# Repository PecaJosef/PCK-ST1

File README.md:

# PCK-ST1
Star tracker with automatic polar alignment

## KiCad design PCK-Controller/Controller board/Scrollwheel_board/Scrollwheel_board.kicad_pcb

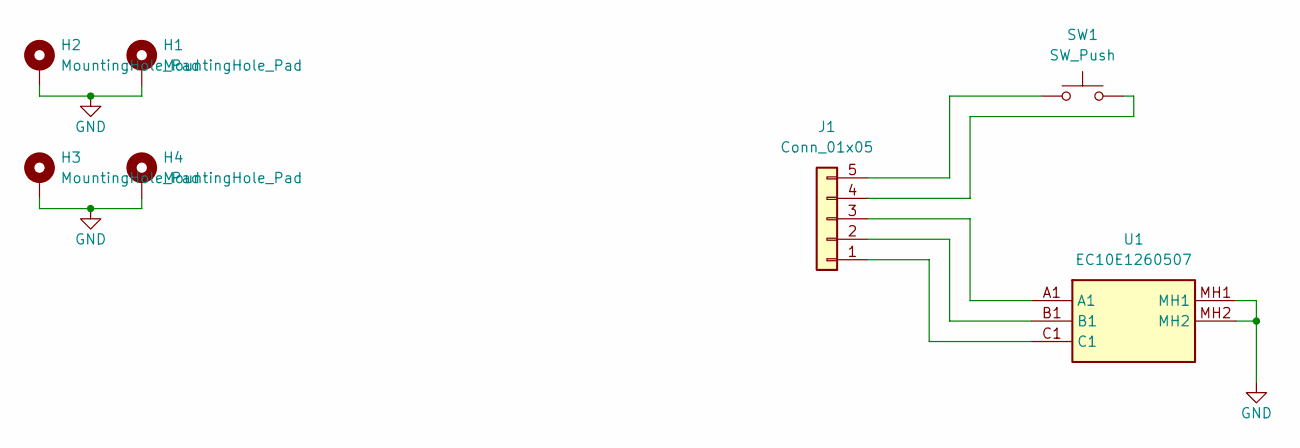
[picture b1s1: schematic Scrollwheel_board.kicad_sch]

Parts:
H1, H2, H3, H4: MountingHole_Pad; MountingHole_3.2mm_M3_DIN965_Pad
J1: Conn_01x05; JST_PH_B5B-PH-K_1x05_P2.00mm_Vertical
SW1: SW_Push; SW_SPST_PTS645Sx43SMTR92
U1: EC10E1260507; Mouser Part Number 688-EC10E1260507

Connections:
GND: H1.1, H2.1, H3.1, H4.1, U1.MH1, U1.MH2
unnamed: J1.1, U1.C1
unnamed: J1.2, U1.B1
unnamed: J1.3, U1.A1
unnamed: J1.4, SW1.2
unnamed: J1.5, SW1.1

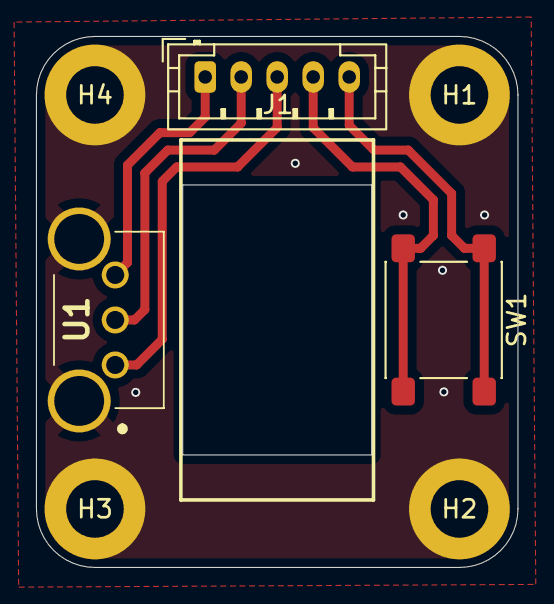
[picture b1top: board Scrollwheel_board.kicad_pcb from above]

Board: 2 copper layers, 26.8 x 29.5 mm, 7 parts (0 on the bottom side), 6 nets.

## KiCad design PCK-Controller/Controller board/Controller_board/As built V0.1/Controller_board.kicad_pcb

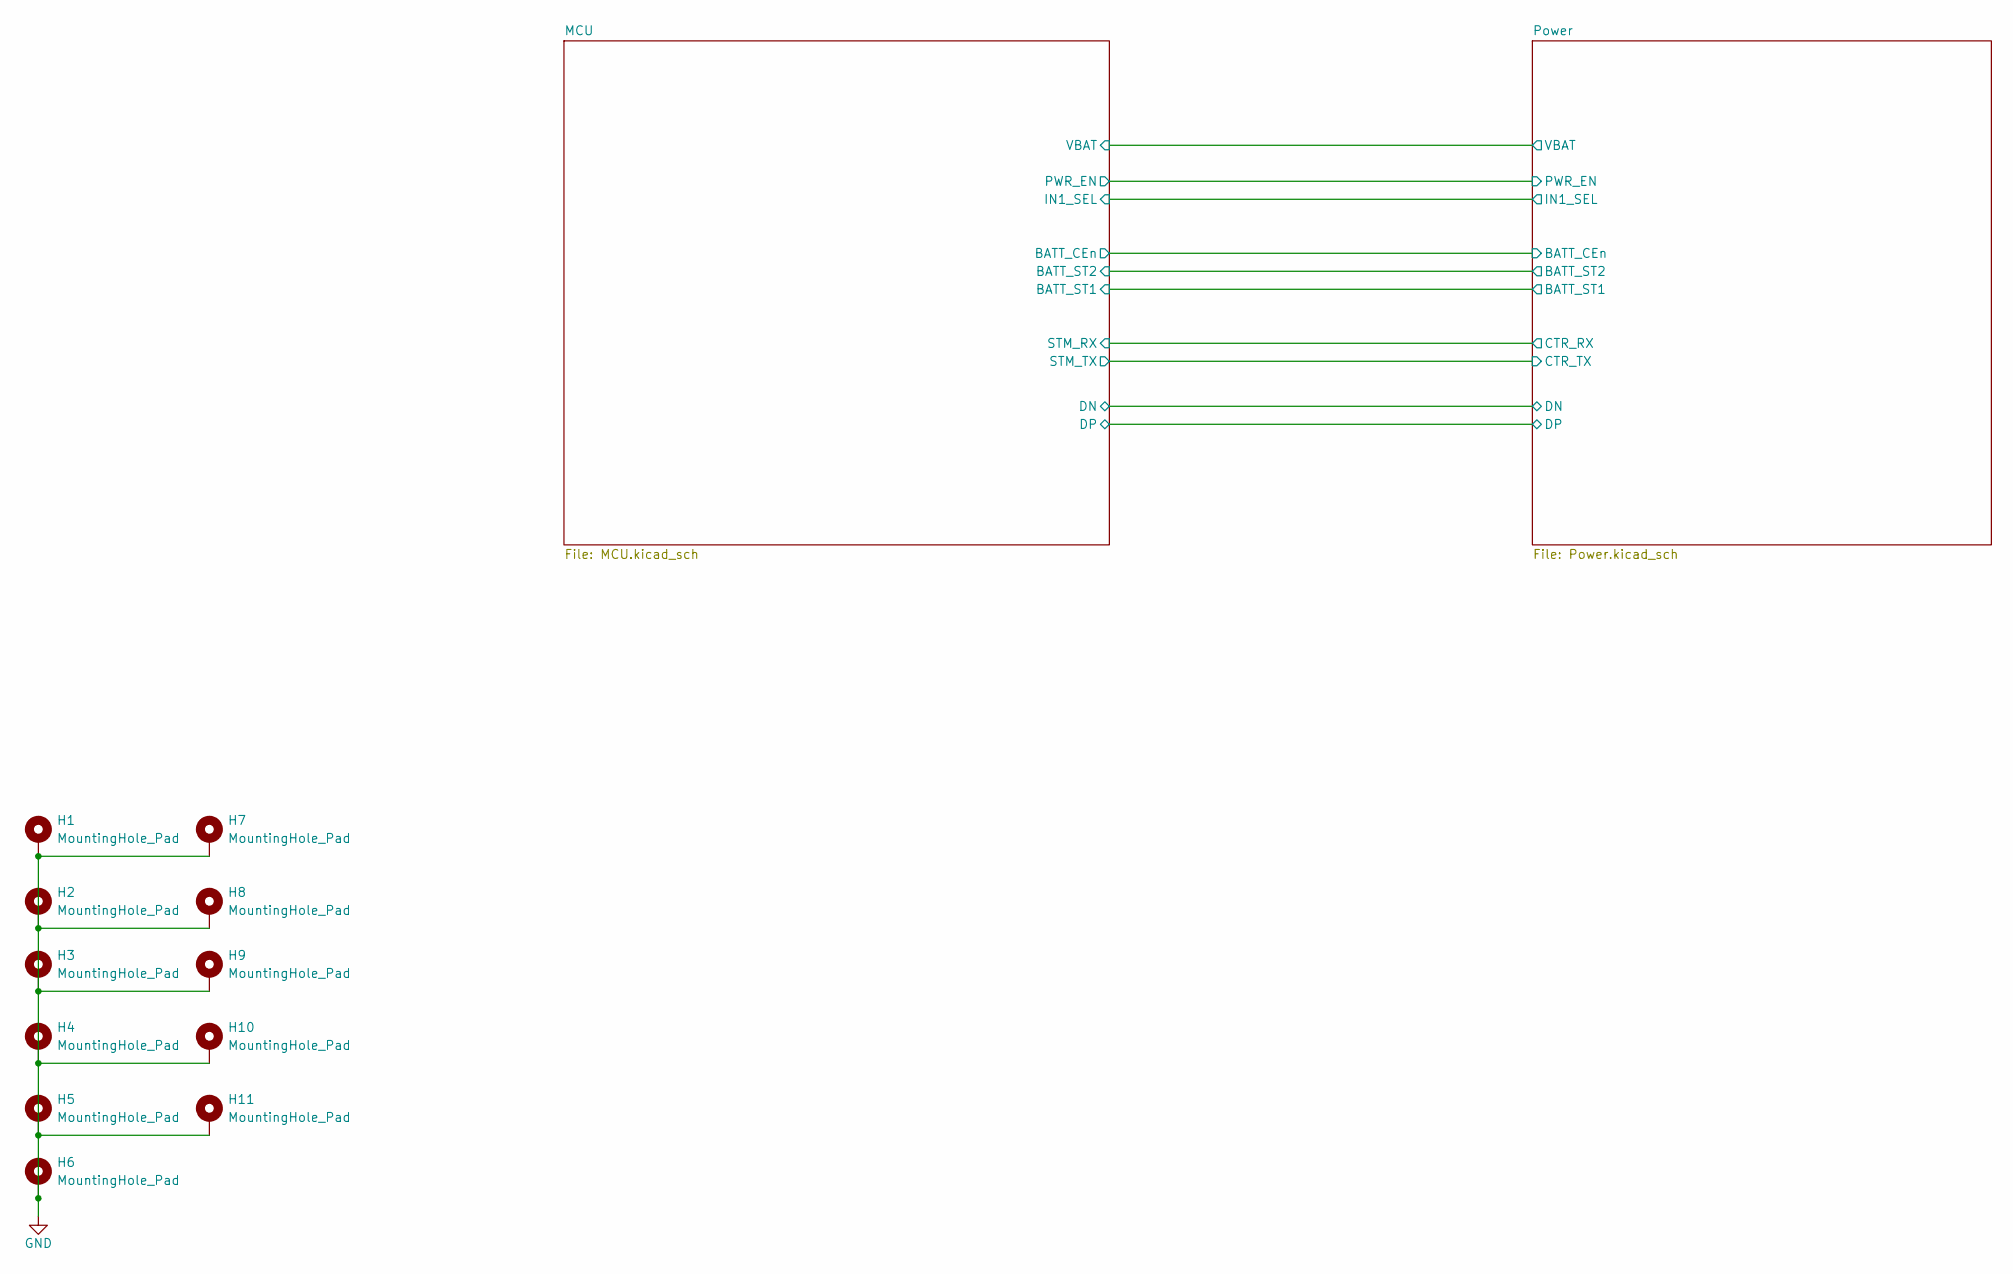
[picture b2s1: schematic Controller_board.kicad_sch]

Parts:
H1, H2, H3, H4, H5, H6, H7, H8, H9, H10, H11: MountingHole_Pad; MountingHole_3.2mm_M3_DIN965_Pad

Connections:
GND: H1.1, H2.1, H3.1, H4.1, H5.1, H6.1, H7.1, H8.1, H9.1, H10.1, H11.1; also elsewhere on the board

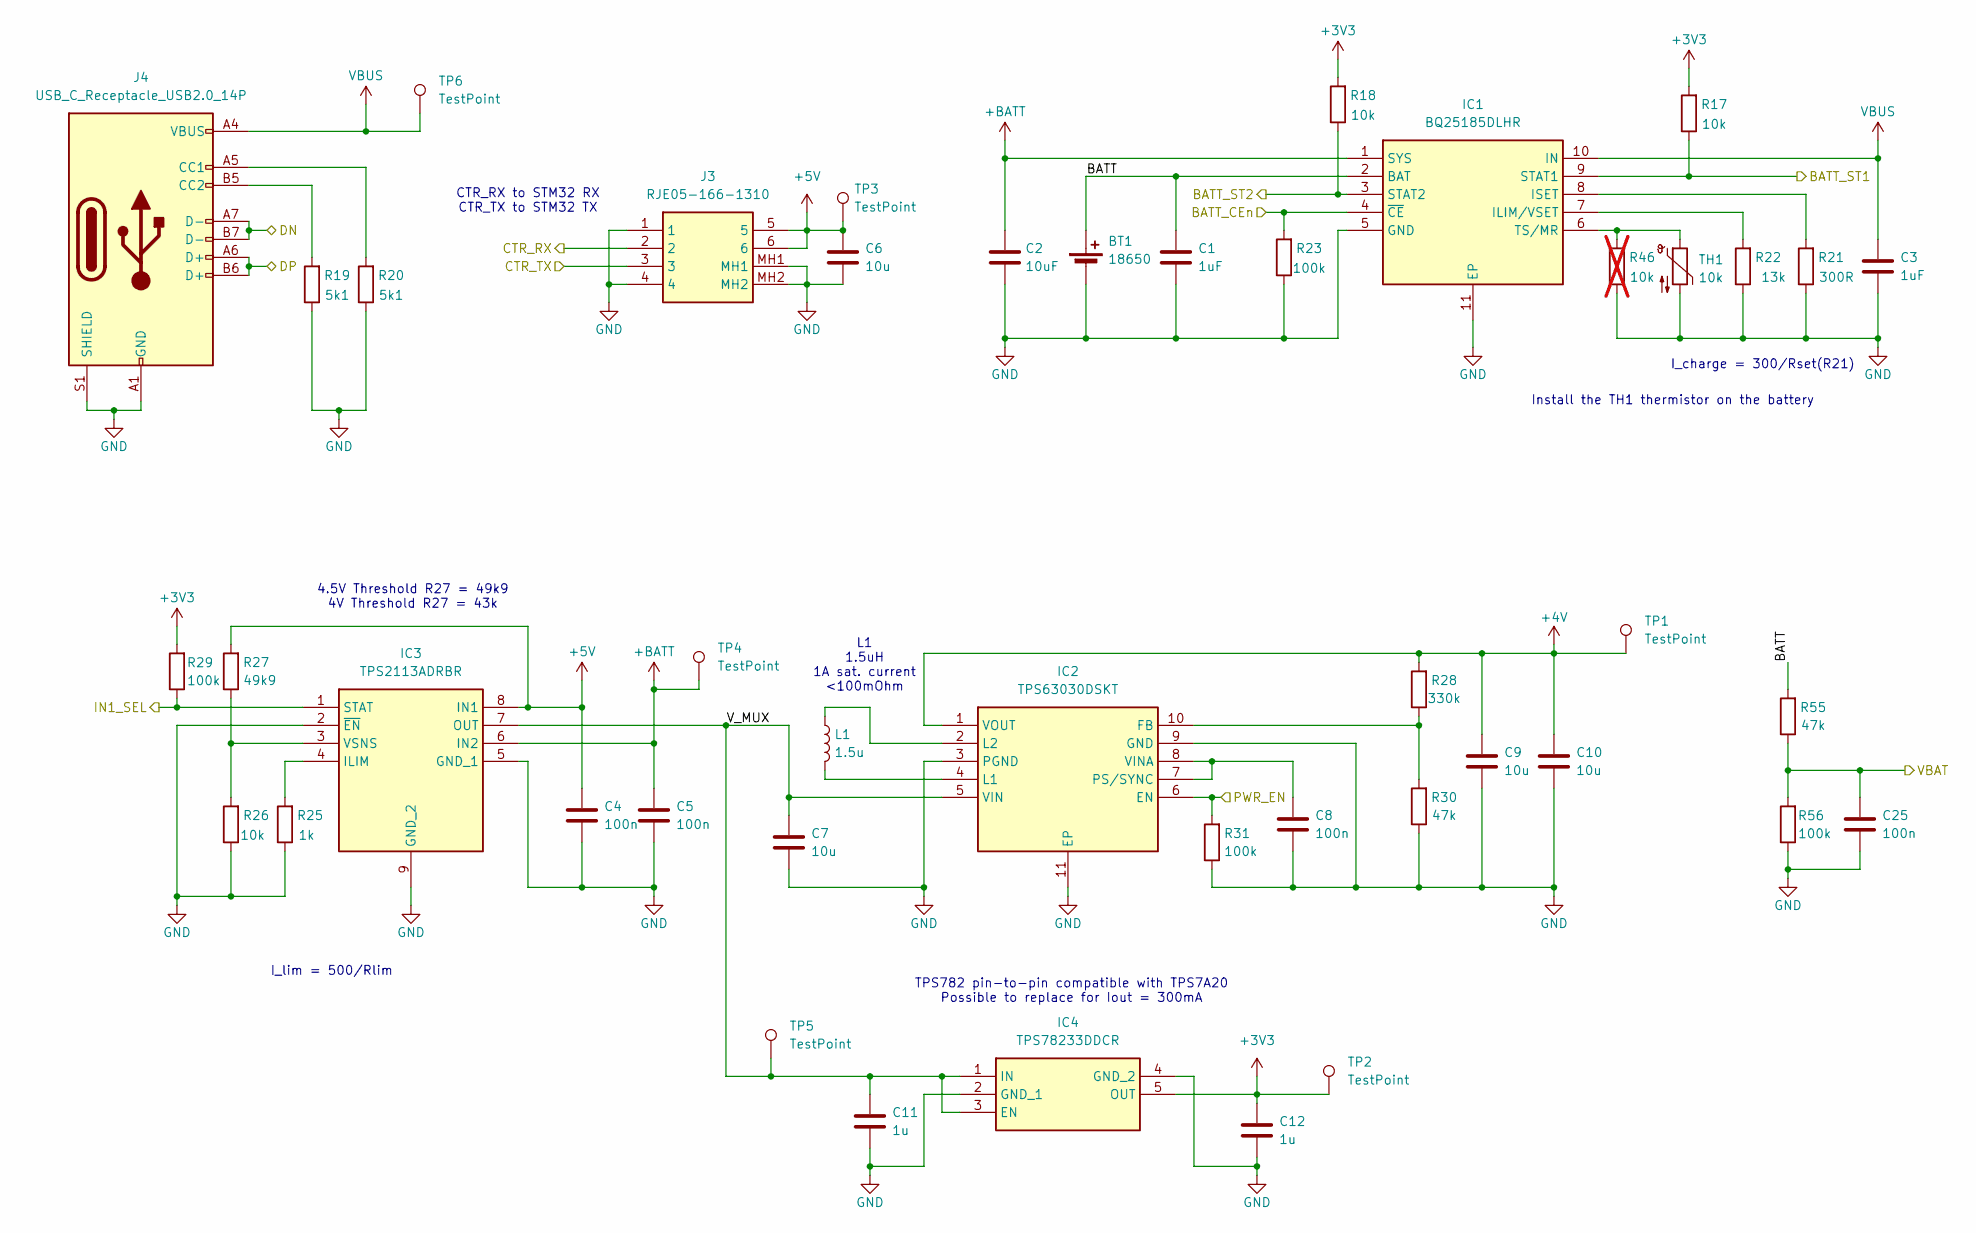
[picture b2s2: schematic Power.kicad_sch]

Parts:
BT1: 18650; BatteryHolder_Keystone_1042_1x18650
C1, C3: 1uF; C_0603_1608Metric
C2: 10uF; C_0603_1608Metric
C4, C5, C8, C25: 100n; C_0603_1608Metric
C6, C7, C9, C10: 10u; C_0603_1608Metric
C11, C12: 1u; C_0603_1608Metric
IC1: BQ25185DLHR; SON40P220X200X80-11N; Mouser Part Number 595-BQ25185DLHR
IC2: TPS63030DSKT; SON50P250X250X80-11N-D; Mouser Part Number 595-TPS63030DSKT
IC3: TPS2113ADRBR; SON65P300X300X100-9N-D; Mouser Part Number 595-TPS2113ADRBR
IC4: TPS78233DDCR; SOT95P280X110-5N; Mouser Part Number 595-TPS78233DDCR
J3: RJE05-166-1310; RJE051661310; Mouser Part Number 523-RJE05-166-1310
J4: USB_C_Receptacle_USB2.0_14P; USB_C_Receptacle_HCTL_HC-TYPE-C-16P-01A
L1: 1.5u; L_1008_2520Metric
R17, R18, R26: 10k; R_0603_1608Metric
R19, R20: 5k1; R_0603_1608Metric
R21: 300R; R_0603_1608Metric
R22: 13k; R_0603_1608Metric
R23, R29, R31, R56: 100k; R_0603_1608Metric
R25: 1k; R_0603_1608Metric
R27: 49k9; R_0603_1608Metric
R28: 330k; R_0603_1608Metric
R30, R55: 47k; R_0603_1608Metric
R46: 10k; R_0603_1608Metric; not fitted
TH1: 10k; JST_PH_B2B-PH-K_1x02_P2.00mm_Vertical
TP1, TP2, TP3, TP4, TP5, TP6: TestPoint; TestPoint_Pad_D1.5mm

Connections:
+3V3: C12.1, IC4.5 (OUT), R17.2, R18.2, R29.2, TP2.1; also elsewhere on the board
+4V: C9.1, C10.1, IC2.1 (VOUT), R28.2, TP1.1; also elsewhere on the board
+5V: C4.1, C6.1, IC3.8 (IN1), J3.5, J3.6, R27.2, TP3.1
+BATT: C2.1, C5.1, IC1.1 (SYS), IC3.6 (IN2), TP4.1
/MCU/BATT_CEn: IC1.4 (~CE), R23.2; also elsewhere on the board
/MCU/BATT_ST1: IC1.9 (STAT1), R17.1; also elsewhere on the board
/MCU/BATT_ST2: IC1.3 (STAT2), R18.1; also elsewhere on the board
/MCU/DN: J4.A7 (D-), J4.B7 (D-); also elsewhere on the board
/MCU/DP: J4.A6 (D+), J4.B6 (D+); also elsewhere on the board
/MCU/IN1_SEL: IC3.1 (STAT), R29.1; also elsewhere on the board
/MCU/PWR_EN: IC2.6 (EN), R31.2; also elsewhere on the board
/MCU/STM_RX: J3.2; also elsewhere on the board
/MCU/STM_TX: J3.3; also elsewhere on the board
/MCU/VBAT: C25.1, R55.1, R56.2; also elsewhere on the board
/Power/BATT: BT1.1 (+), C1.1, IC1.2 (BAT), R55.2
/Power/V_MUX: C7.1, C11.1, IC2.5 (VIN), IC3.7 (OUT), IC4.1 (IN), IC4.3 (EN), TP5.1
GND: BT1.2 (-), C1.2, C2.2, C3.2, C4.2, C5.2, C6.2, C7.2, C8.2, C9.2, C10.2, C11.2, C12.2, C25.2, IC1.5 (GND), IC1.11 (EP), IC2.3 (PGND), IC2.9 (GND), IC2.11 (EP), IC3.2 (~EN), IC3.5 (GND_1), IC3.9 (GND_2), IC4.2 (GND_1), IC4.4 (GND_2), J3.1, J3.4, J3.MH1, J3.MH2, J4.A1 (GND), J4.A12 (GND), J4.B1 (GND), J4.B12 (GND), J4.S1 (SHIELD), R19.1, R20.1, R21.1, R22.1, R23.1, R25.1, R26.1, R30.1, R31.1, R46.1, R56.1, TH1.2; also elsewhere on the board
unnamed: IC1.7 (ILIM/VSET), R22.2
unnamed: IC1.8 (ISET), R21.2
unnamed: IC1.6 (TS/MR), R46.2, TH1.1
unnamed: IC2.10 (FB), R28.1, R30.2
unnamed: IC2.4 (L1), L1.2
unnamed: IC2.2 (L2), L1.1
unnamed: C8.1, IC2.7 (PS/SYNC), IC2.8 (VINA)
unnamed: IC3.4 (ILIM), R25.2
unnamed: IC3.3 (VSNS), R26.2, R27.1
unnamed: J4.A5 (CC1), R20.2
unnamed: J4.B5 (CC2), R19.2
VBUS: C3.1, IC1.10 (IN), J4.A4 (VBUS), J4.A9 (VBUS), J4.B4 (VBUS), J4.B9 (VBUS), TP6.1

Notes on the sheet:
CTR_RX to STM32 RX CTR_TX to STM32 TX
Install the TH1 thermistor on the battery
I_charge = 300/Rset(R21)
I_lim = 500/Rlim
4.5V Threshold R27 = 49k9 4V Threshold R27 = 43k
TPS782 pin-to-pin compatible with TPS7A20 Possible to replace for Iout = 300mA
L1 1.5uH 1A sat. current <100mOhm

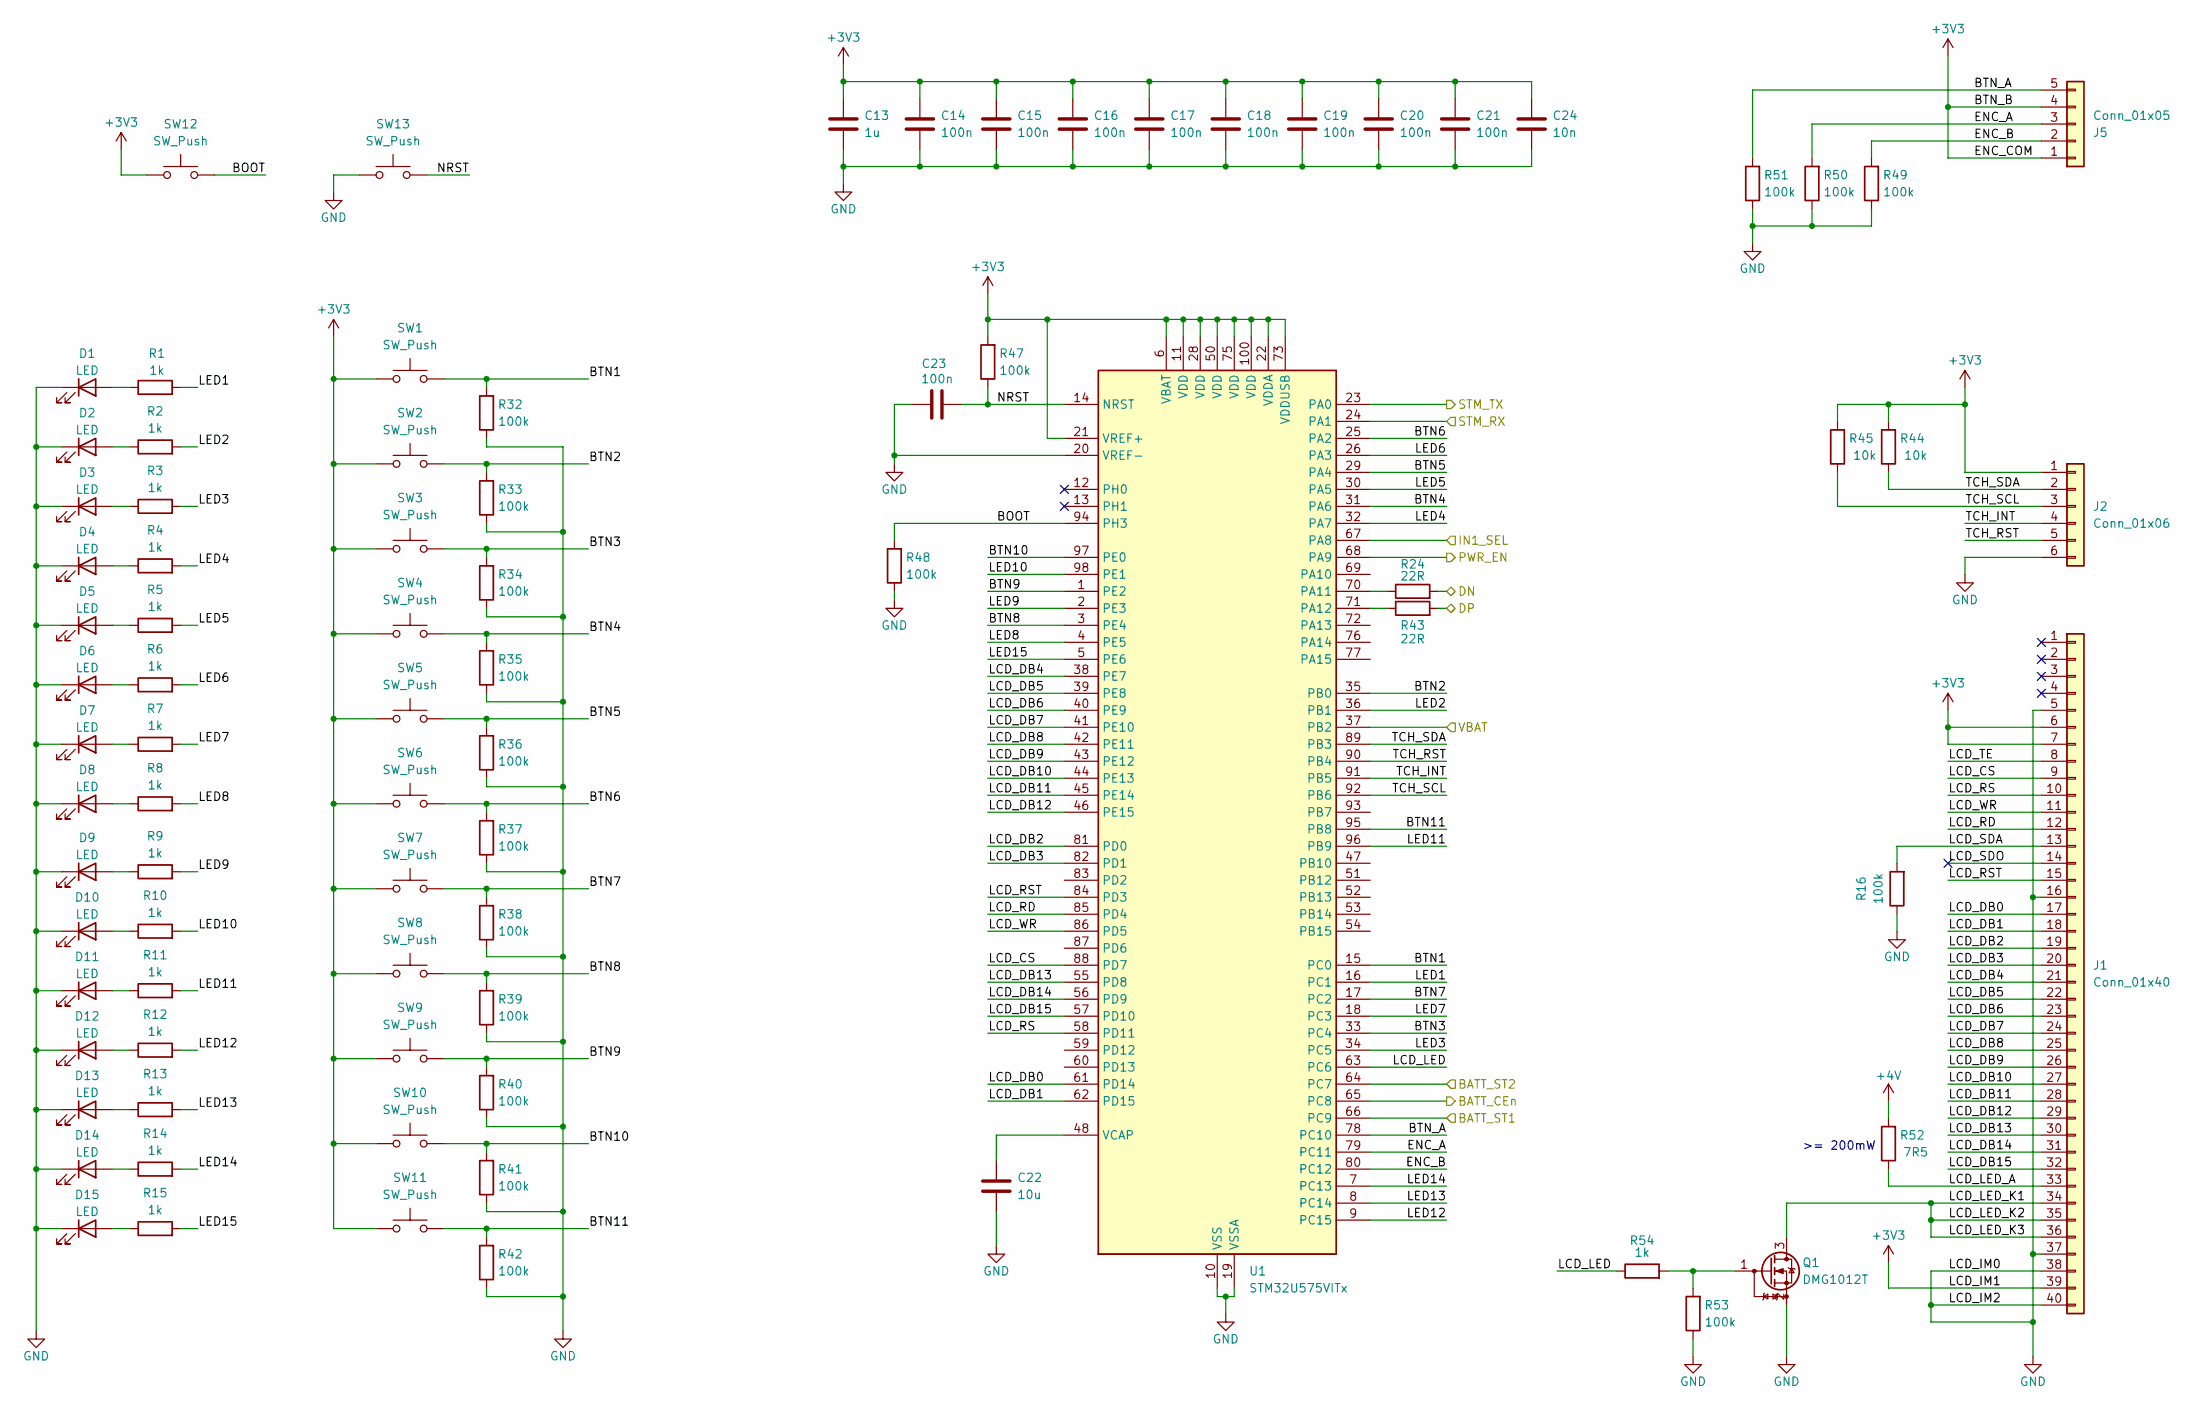
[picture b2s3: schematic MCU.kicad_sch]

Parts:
C13: 1u; C_0603_1608Metric
C14, C15, C16, C17, C18, C19, C20, C21, C23: 100n; C_0603_1608Metric
C22: 10u; C_0603_1608Metric
C24: 10n; C_0603_1608Metric
D1, D2, D3, D4, D5, D6, D7, D8, D9, D10, D11, D12, D13, D14, D15: LED; LED_0603_1608Metric
J1: Conn_01x40; FPC_P0.50mm_Horizontal_40P
J2: Conn_01x06; Hirose_FH12-6S-0.5SH_1x06-1MP_P0.50mm_Horizontal
J5: Conn_01x05; JST_PH_B5B-PH-K_1x05_P2.00mm_Vertical
Q1: DMG1012T; SOT-523
R1, R2, R3, R4, R5, R6, R7, R8, R9, R10, R11, R12, R13, R14, R15, R54: 1k; R_0603_1608Metric
R16, R32, R33, R34, R35, R36, R37, R38, R39, R40, R41, R42, R47, R48, R49, R50, R51, R53: 100k; R_0603_1608Metric
R24, R43: 22R; R_0603_1608Metric
R44, R45: 10k; R_0603_1608Metric
R52: 7R5; R_0805_2012Metric
SW1, SW2, SW3, SW4, SW5, SW6, SW7, SW8, SW9, SW10, SW11, SW12, SW13: SW_Push; SW_SPST_PTS645Sx43SMTR92
U1: STM32U575VITx; LQFP-100_14x14mm_P0.5mm

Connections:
+3V3: C13.1, C14.1, C15.1, C16.1, C17.1, C18.1, C19.1, C20.1, C21.1, C24.1, J1.6, J1.7, J1.39, J2.1, J5.1, J5.4, R44.2, R45.2, R47.2, SW1.1, SW2.1, SW3.1, SW4.1, SW5.1, SW6.1, SW7.1, SW8.1, SW9.1, SW10.1, SW11.1, SW12.1, U1.6 (VBAT), U1.11 (VDD), U1.21 (VREF+), U1.22 (VDDA), U1.28 (VDD), U1.50 (VDD), U1.73 (VDDUSB), U1.75 (VDD), U1.100 (VDD); also elsewhere on the board
+4V: R52.2; also elsewhere on the board
/MCU/BATT_CEn: U1.65 (PC8); also elsewhere on the board
/MCU/BATT_ST1: U1.66 (PC9); also elsewhere on the board
/MCU/BATT_ST2: U1.64 (PC7); also elsewhere on the board
/MCU/BOOT: R48.2, SW12.2, U1.94 (PH3)
/MCU/BTN1: R32.2, SW1.2, U1.15 (PC0)
/MCU/BTN2: R33.2, SW2.2, U1.35 (PB0)
/MCU/BTN3: R34.2, SW3.2, U1.33 (PC4)
/MCU/BTN4: R35.2, SW4.2, U1.31 (PA6)
/MCU/BTN5: R36.2, SW5.2, U1.29 (PA4)
/MCU/BTN6: R37.2, SW6.2, U1.25 (PA2)
/MCU/BTN7: R38.2, SW7.2, U1.17 (PC2)
/MCU/BTN8: R39.2, SW8.2, U1.3 (PE4)
/MCU/BTN9: R40.2, SW9.2, U1.1 (PE2)
/MCU/BTN10: R41.2, SW10.2, U1.97 (PE0)
/MCU/BTN11: R42.2, SW11.2, U1.95 (PB8)
/MCU/BTN_A: J5.5, R51.2, U1.78 (PC10)
/MCU/DN: R24.2; also elsewhere on the board
/MCU/DP: R43.2; also elsewhere on the board
/MCU/ENC_A: J5.3, R50.2, U1.79 (PC11)
/MCU/ENC_B: J5.2, R49.2, U1.80 (PC12)
/MCU/IN1_SEL: U1.67 (PA8); also elsewhere on the board
/MCU/LCD_CS: J1.9, U1.88 (PD7)
/MCU/LCD_DB0: J1.17, U1.61 (PD14)
/MCU/LCD_DB1: J1.18, U1.62 (PD15)
/MCU/LCD_DB2: J1.19, U1.81 (PD0)
/MCU/LCD_DB3: J1.20, U1.82 (PD1)
/MCU/LCD_DB4: J1.21, U1.38 (PE7)
/MCU/LCD_DB5: J1.22, U1.39 (PE8)
/MCU/LCD_DB6: J1.23, U1.40 (PE9)
/MCU/LCD_DB7: J1.24, U1.41 (PE10)
/MCU/LCD_DB8: J1.25, U1.42 (PE11)
/MCU/LCD_DB9: J1.26, U1.43 (PE12)
/MCU/LCD_DB10: J1.27, U1.44 (PE13)
/MCU/LCD_DB11: J1.28, U1.45 (PE14)
/MCU/LCD_DB12: J1.29, U1.46 (PE15)
/MCU/LCD_DB13: J1.30, U1.55 (PD8)
/MCU/LCD_DB14: J1.31, U1.56 (PD9)
/MCU/LCD_DB15: J1.32, U1.57 (PD10)
/MCU/LCD_LED: R54.1, U1.63 (PC6)
/MCU/LCD_LED_A: J1.33, R52.1
/MCU/LCD_LED_K1: J1.34, J1.35, J1.36, Q1.3 (D)
/MCU/LCD_RD: J1.12, U1.85 (PD4)
/MCU/LCD_RS: J1.10, U1.58 (PD11)
/MCU/LCD_RST: J1.15, U1.84 (PD3)
/MCU/LCD_SDA: J1.13, R16.2
/MCU/LCD_SDO: J1.14
/MCU/LCD_TE: J1.8
/MCU/LCD_WR: J1.11, U1.86 (PD5)
/MCU/LED1: R1.2, U1.16 (PC1)
/MCU/LED2: R2.2, U1.36 (PB1)
/MCU/LED3: R3.2, U1.34 (PC5)
/MCU/LED4: R4.2, U1.32 (PA7)
/MCU/LED5: R5.2, U1.30 (PA5)
/MCU/LED6: R6.2, U1.26 (PA3)
/MCU/LED7: R7.2, U1.18 (PC3)
/MCU/LED8: R8.2, U1.4 (PE5)
/MCU/LED9: R9.2, U1.2 (PE3)
/MCU/LED10: R10.2, U1.98 (PE1)
/MCU/LED11: R11.2, U1.96 (PB9)
/MCU/LED12: R12.2, U1.9 (PC15)
/MCU/LED13: R13.2, U1.8 (PC14)
/MCU/LED14: R14.2, U1.7 (PC13)
/MCU/LED15: R15.2, U1.5 (PE6)
/MCU/NRST: C23.2, R47.1, SW13.2, U1.14 (NRST)
/MCU/PWR_EN: U1.68 (PA9); also elsewhere on the board
/MCU/STM_RX: U1.24 (PA1); also elsewhere on the board
/MCU/STM_TX: U1.23 (PA0); also elsewhere on the board
/MCU/TCH_INT: J2.4, U1.91 (PB5)
/MCU/TCH_RST: J2.5, U1.90 (PB4)
/MCU/TCH_SCL: J2.3, R45.1, U1.92 (PB6)
/MCU/TCH_SDA: J2.2, R44.1, U1.89 (PB3)
/MCU/VBAT: U1.37 (PB2); also elsewhere on the board
GND: C13.2, C14.2, C15.2, C16.2, C17.2, C18.2, C19.2, C20.2, C21.2, C22.2, C23.1, C24.2, D1.1 (K), D2.1 (K), D3.1 (K), D4.1 (K), D5.1 (K), D6.1 (K), D7.1 (K), D8.1 (K), D9.1 (K), D10.1 (K), D11.1 (K), D12.1 (K), D13.1 (K), D14.1 (K), D15.1 (K), J1.5, J1.16, J1.37, J1.38, J1.40, J2.6, Q1.2 (S), R16.1, R32.1, R33.1, R34.1, R35.1, R36.1, R37.1, R38.1, R39.1, R40.1, R41.1, R42.1, R48.1, R49.1, R50.1, R51.1, R53.1, SW13.1, U1.10 (VSS), U1.19 (VSSA), U1.20 (VREF-), U1.27 (VSS), U1.49 (VSS), U1.74 (VSS), U1.99 (VSS); also elsewhere on the board
unnamed: D1.2 (A), R1.1
unnamed: D2.2 (A), R2.1
unnamed: D3.2 (A), R3.1
unnamed: D4.2 (A), R4.1
unnamed: D5.2 (A), R5.1
unnamed: D6.2 (A), R6.1
unnamed: D7.2 (A), R7.1
unnamed: D8.2 (A), R8.1
unnamed: D9.2 (A), R9.1
unnamed: D10.2 (A), R10.1
unnamed: D11.2 (A), R11.1
unnamed: D12.2 (A), R12.1
unnamed: D13.2 (A), R13.1
unnamed: D14.2 (A), R14.1
unnamed: D15.2 (A), R15.1
unnamed: Q1.1 (G), R53.2, R54.2
unnamed: R24.1, U1.70 (PA11)
unnamed: R43.1, U1.71 (PA12)
unnamed: C22.1, U1.48 (VCAP)

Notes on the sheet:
>= 200mW

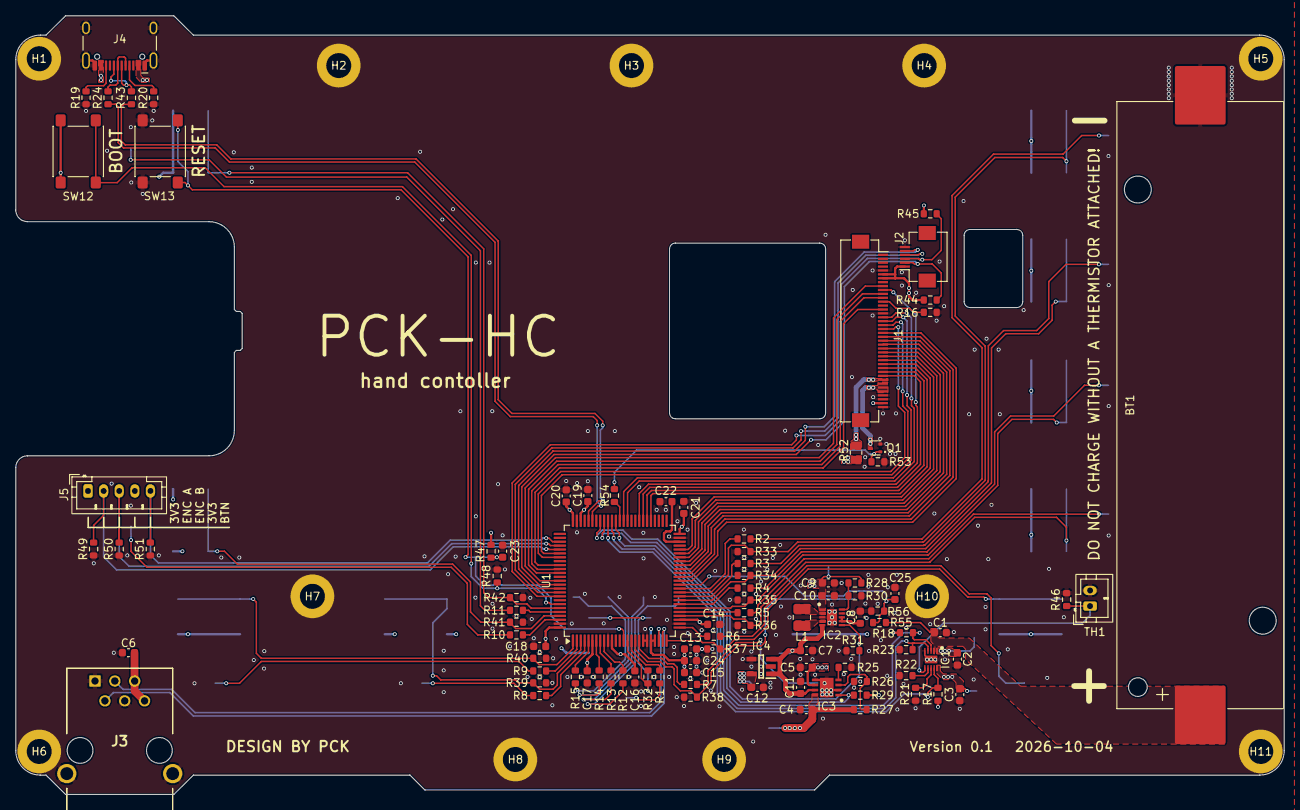
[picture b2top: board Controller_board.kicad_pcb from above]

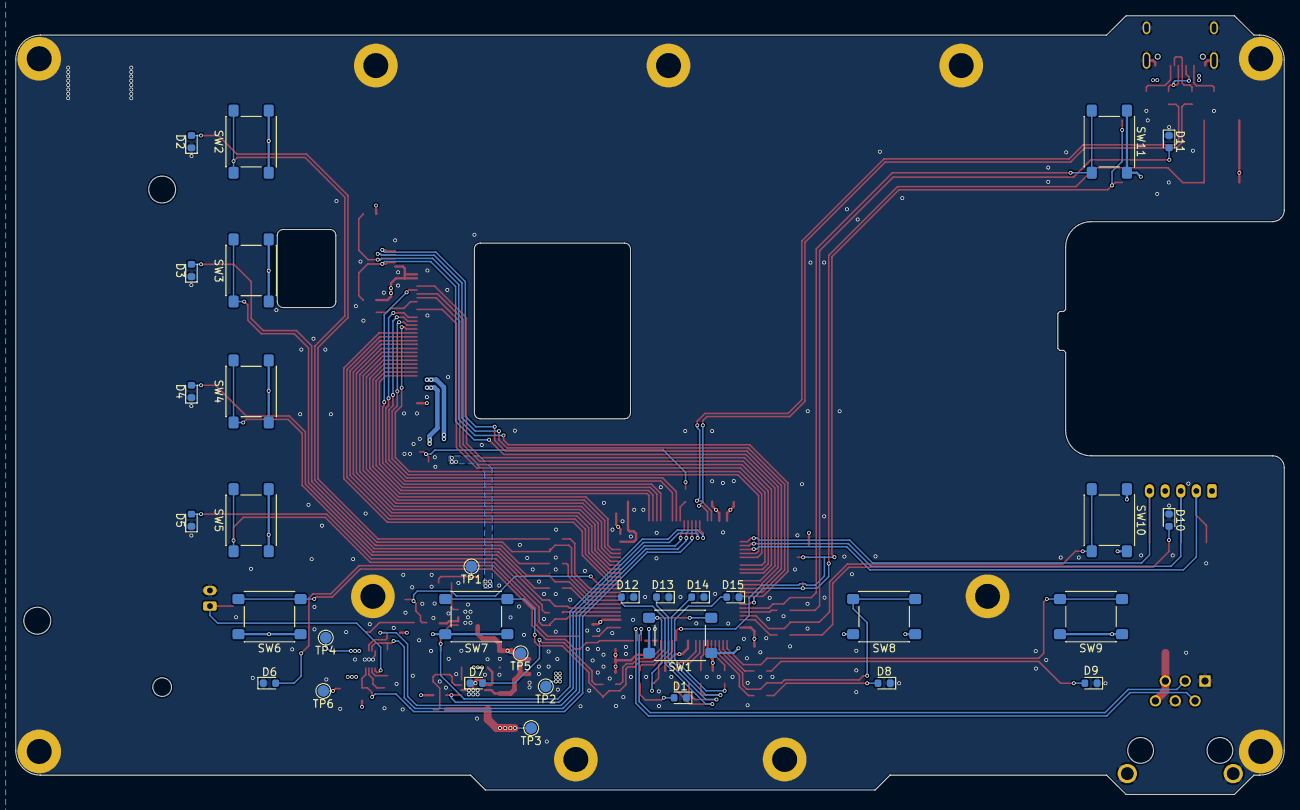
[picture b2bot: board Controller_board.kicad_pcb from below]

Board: 4 copper layers, 162.5 x 99.8 mm, 140 parts (32 on the bottom side), 108 nets.

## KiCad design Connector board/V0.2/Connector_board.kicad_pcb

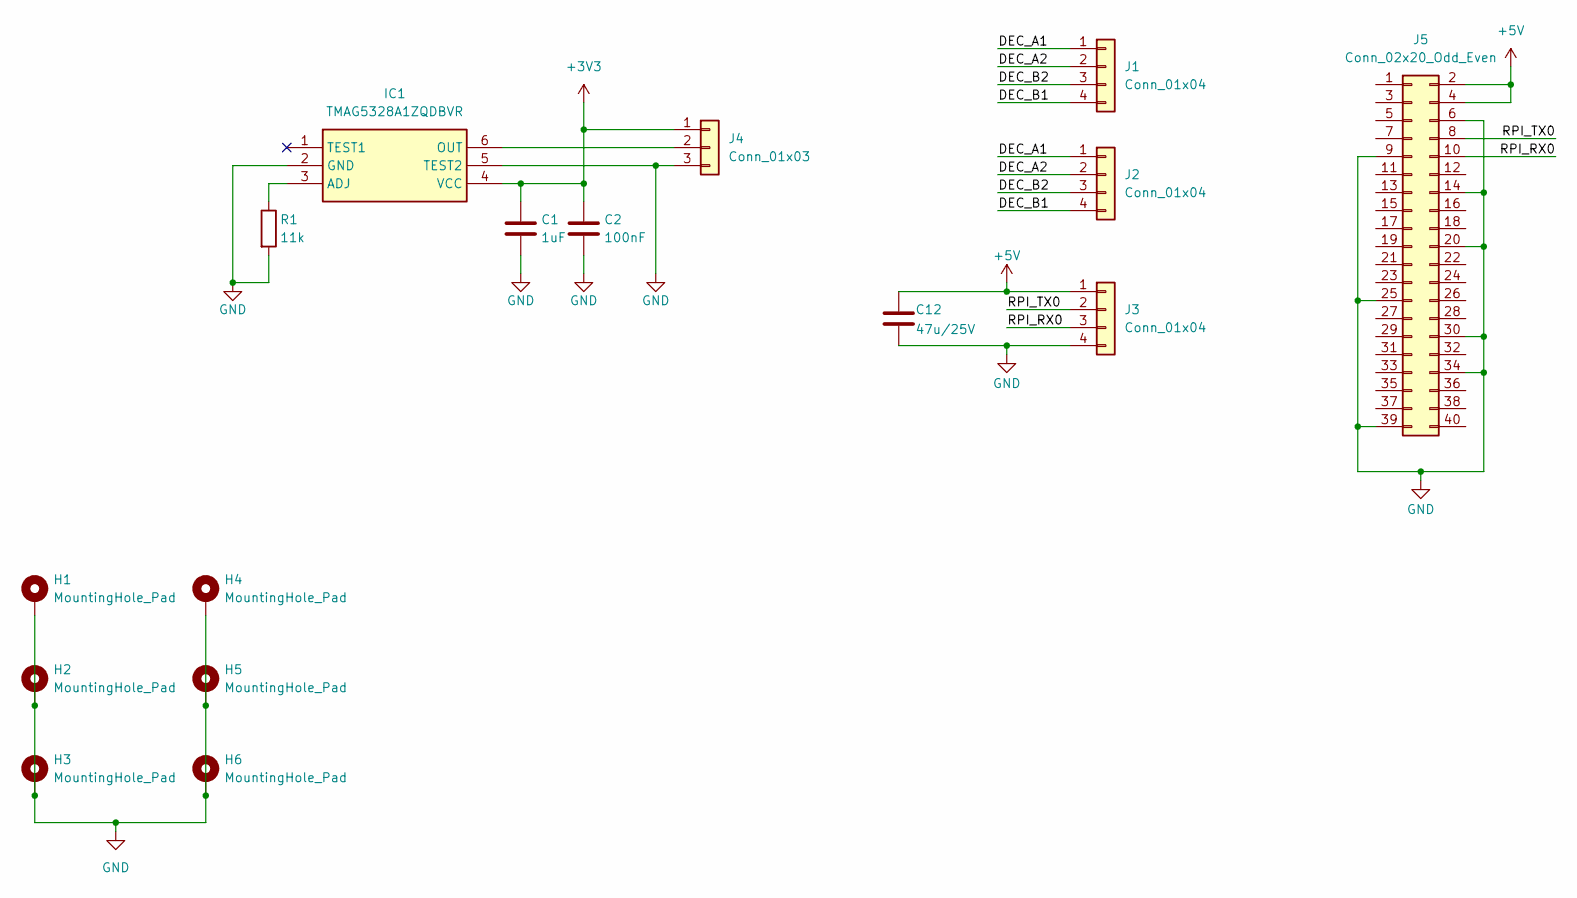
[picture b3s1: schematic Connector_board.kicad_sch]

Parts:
C1: 1uF; C_0402_1005Metric
C2: 100nF; C_0402_1005Metric
C12: 47u/25V; C_1206_3216Metric; Part Number C3216X5R1E476M160AC
H1, H2, H3, H4, H5, H6: MountingHole_Pad; MountingHole_2.5mm_Pad
IC1: TMAG5328A1ZQDBVR; SOT95P280X145-6N; Manufacturer_Part_Number TMAG5328A1ZQDBVR
J1, J3: Conn_01x04; JST_PH_B4B-PH-K_1x04_P2.00mm_Vertical
J2: Conn_01x04; JST_PH_S4B-PH-SM4-TB_1x04-1MP_P2.00mm_Horizontal
J4: Conn_01x03; JST_PH_B3B-PH-K_1x03_P2.00mm_Vertical
J5: Conn_02x20_Odd_Even; PinSocket_2x20_P2.54mm_Vertical
R1: 11k; R_0402_1005Metric

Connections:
+3V3: C1.1, C2.1, IC1.4 (VCC), J4.1
+5V: C12.1, J3.1, J5.2, J5.4
/DEC_A1: J1.1, J2.1
/DEC_A2: J1.2, J2.2
/DEC_B1: J1.4, J2.4
/DEC_B2: J1.3, J2.3
/RPI_RX0: J3.3, J5.10
/RPI_TX0: J3.2, J5.8
GND: C1.2, C2.2, C12.2, H1.1, H2.1, H3.1, H4.1, H5.1, H6.1, IC1.2 (GND), IC1.5 (TEST2), J3.4, J4.3, J5.6, J5.9, J5.14, J5.20, J5.25, J5.30, J5.34, J5.39, R1.2
unnamed: IC1.3 (ADJ), R1.1
unnamed: IC1.6 (OUT), J4.2

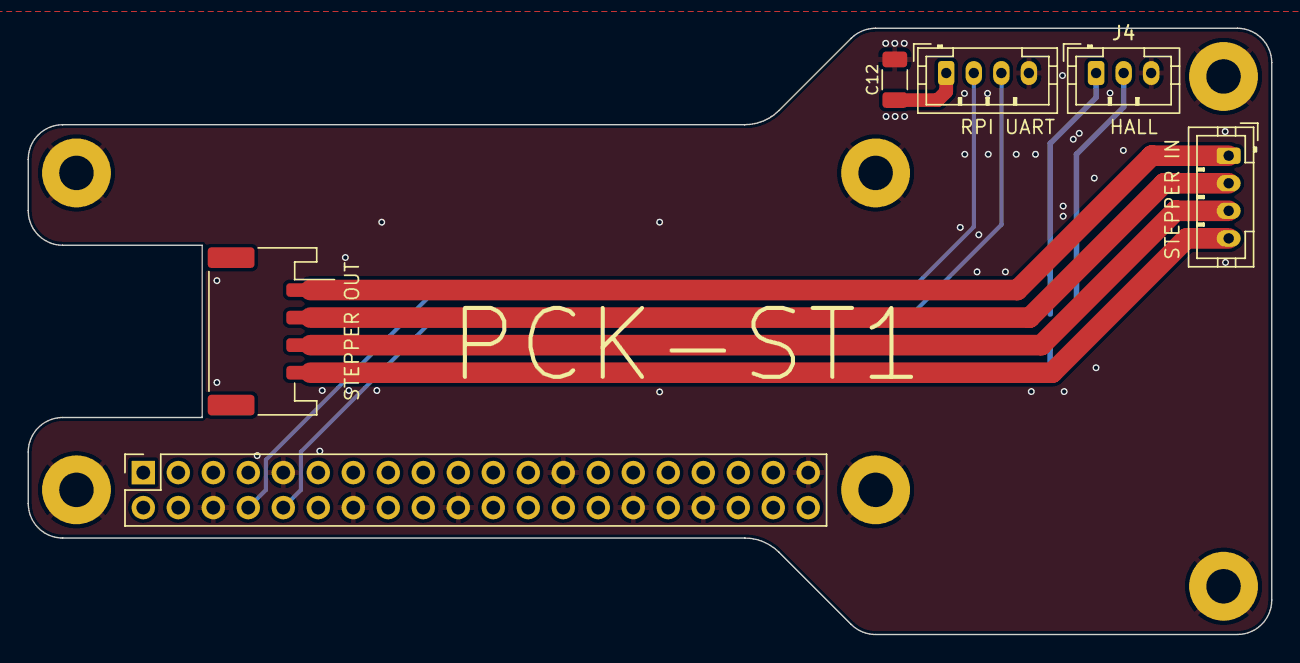
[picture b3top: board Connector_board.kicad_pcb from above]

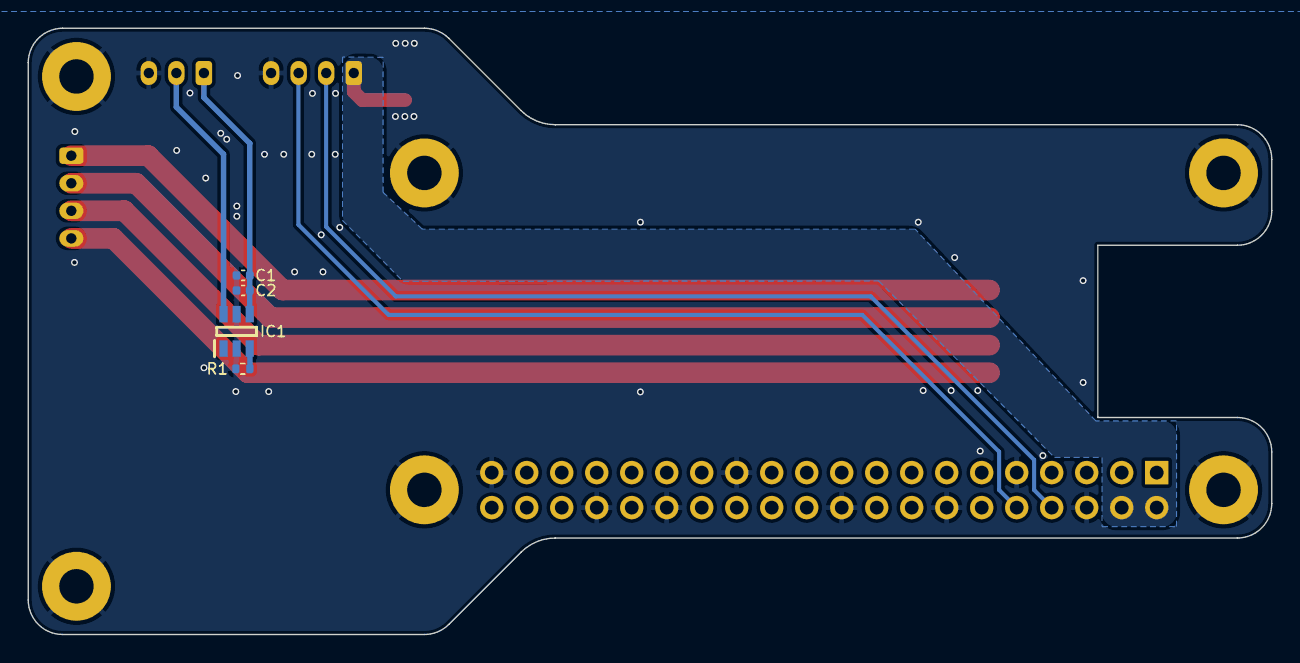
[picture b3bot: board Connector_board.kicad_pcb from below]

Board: 2 copper layers, 90.2 x 44.0 mm, 16 parts (4 on the bottom side), 11 nets.
